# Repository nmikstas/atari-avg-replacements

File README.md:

# atari-avg-replacements
Atari AVG chip replacements.  Both CPLD andTTL versions of the chip.

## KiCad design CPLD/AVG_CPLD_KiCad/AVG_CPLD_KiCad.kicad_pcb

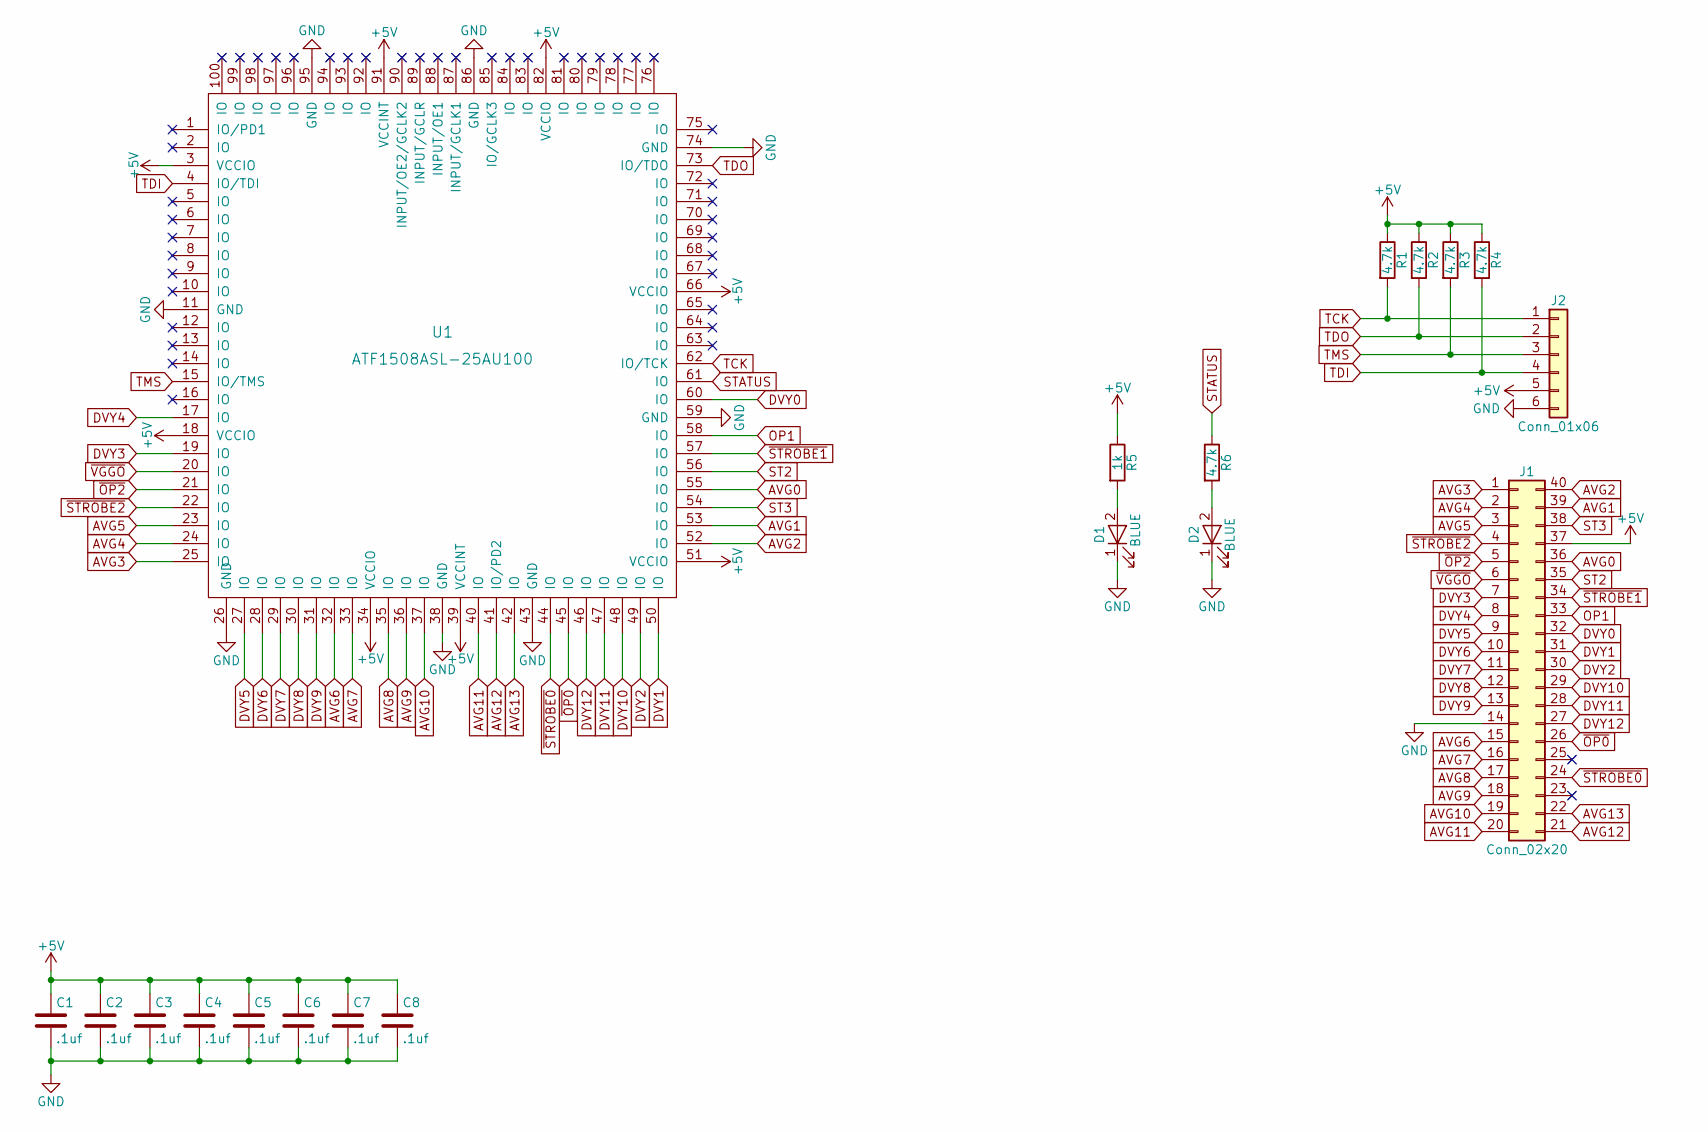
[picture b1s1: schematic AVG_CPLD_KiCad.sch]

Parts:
C1, C2, C3, C4, C5, C6, C7, C8: .1uf; 0402
D1, D2: BLUE; D_0805
J1: Conn_02x20; DDIP40
J2: Conn_01x06; SIP6
R1, R2, R3, R4, R6: 4.7k; R_0805_HandSoldering
R5: 1k; R_0805_HandSoldering
U1: ATF1508ASL-25AU100; CPLD

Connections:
+5V: C1.1, C2.1, C3.1, C4.1, C5.1, C6.1, C7.1, C8.1, J1.37, J2.5, R1.1, R2.1, R3.1, R4.1, R5.1, U1.3 (VCCIO), U1.18 (VCCIO), U1.34 (VCCIO), U1.39 (VCCINT), U1.51 (VCCIO), U1.66 (VCCIO), U1.82 (VCCIO), U1.91 (VCCINT)
AVG0: J1.36, U1.55 (IO)
AVG1: J1.39, U1.53 (IO)
AVG2: J1.40, U1.52 (IO)
AVG3: J1.1, U1.25 (IO)
AVG4: J1.2, U1.24 (IO)
AVG5: J1.3, U1.23 (IO)
AVG6: J1.15, U1.32 (IO)
AVG7: J1.16, U1.33 (IO)
AVG8: J1.17, U1.35 (IO)
AVG9: J1.18, U1.36 (IO)
AVG10: J1.19, U1.37 (IO)
AVG11: J1.20, U1.40 (IO)
AVG12: J1.21, U1.41 (IO/PD2)
AVG13: J1.22, U1.42 (IO)
DVY0: J1.32, U1.60 (IO)
DVY1: J1.31, U1.50 (IO)
DVY2: J1.30, U1.49 (IO)
DVY3: J1.7, U1.19 (IO)
DVY4: J1.8, U1.17 (IO)
DVY5: J1.9, U1.27 (IO)
DVY6: J1.10, U1.28 (IO)
DVY7: J1.11, U1.29 (IO)
DVY8: J1.12, U1.30 (IO)
DVY9: J1.13, U1.31 (IO)
DVY10: J1.29, U1.48 (IO)
DVY11: J1.28, U1.47 (IO)
DVY12: J1.27, U1.46 (IO)
GND: C1.2, C2.2, C3.2, C4.2, C5.2, C6.2, C7.2, C8.2, D1.1 (K), D2.1 (K), J1.14, J2.6, U1.11 (GND), U1.26 (GND), U1.38 (GND), U1.43 (GND), U1.59 (GND), U1.74 (GND), U1.86 (GND), U1.95 (GND)
unnamed: D1.2 (A), R5.2
unnamed: D2.2 (A), R6.2
OP1: J1.33, U1.58 (IO)
ST2: J1.35, U1.56 (IO)
ST3: J1.38, U1.54 (IO)
STATUS: R6.1, U1.61 (IO)
TCK: J2.1, R1.2, U1.62 (IO/TCK)
TDI: J2.4, R4.2, U1.4 (IO/TDI)
TDO: J2.2, R2.2, U1.73 (IO/TDO)
TMS: J2.3, R3.2, U1.15 (IO/TMS)
~OP0: J1.26, U1.45 (IO)
~OP2: J1.5, U1.21 (IO)
~STROBE0: J1.24, U1.44 (IO)
~STROBE1: J1.34, U1.57 (IO)
~STROBE2: J1.4, U1.22 (IO)
~VGGO: J1.6, U1.20 (IO)

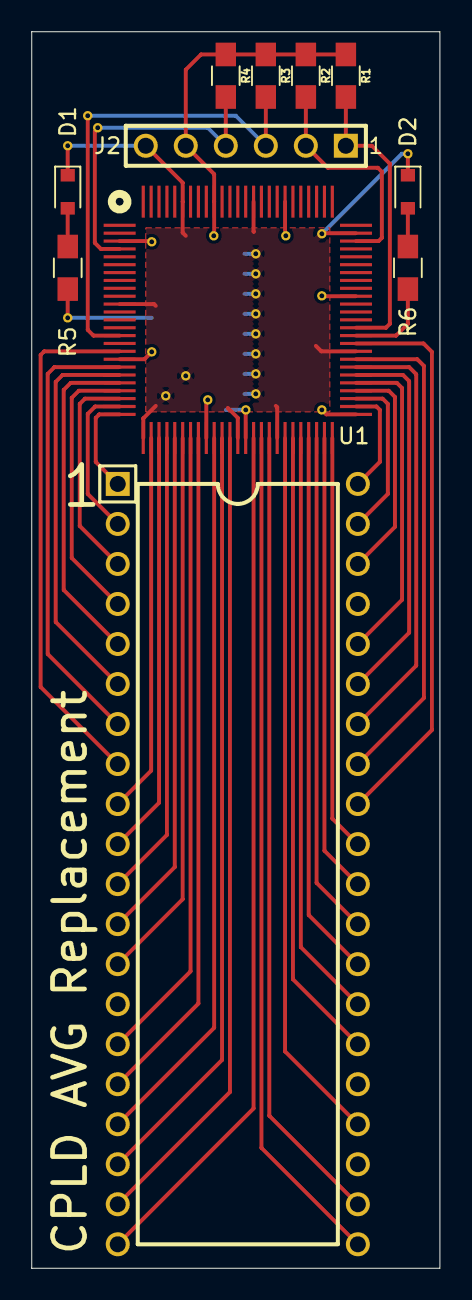
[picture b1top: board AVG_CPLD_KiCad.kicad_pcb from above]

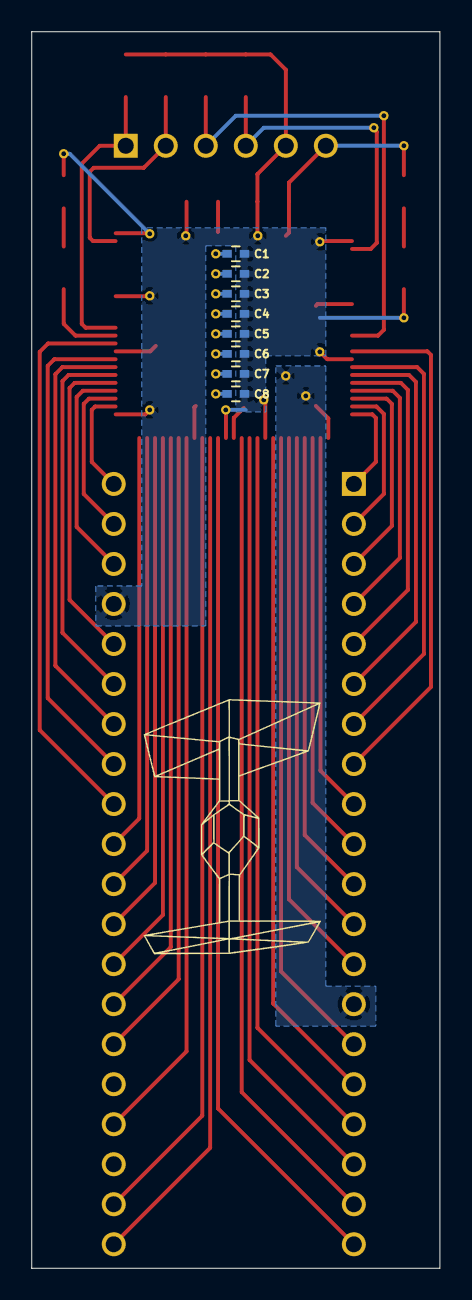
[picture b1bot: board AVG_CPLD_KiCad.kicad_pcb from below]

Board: 2 copper layers, 25.9 x 78.5 mm, 19 parts (8 on the bottom side), 45 nets.

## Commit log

2020-03-17 Transferred project into github
